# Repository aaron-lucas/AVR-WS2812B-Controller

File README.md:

LED Strip Controller
==========================

Project Description:
---------------------
This project uses an Atmel ATtiny85 microcontroller to light up a strip of WS2812B LEDs with a set of 12 pre-defined patterns without relying on external libraries.

It is easy to create custom patterns as each LED is independently controlled.

A PCB design is included which allows the microcontroller and LED strip to be powered over a micro USB (type B) connection, with a toggle switch to turn the LED strip on or off and a Cherry-MX style button to cycle between the display modes.

Colors and Patterns:
---------------------

There are 12 pre-defined patterns programmed by default including 9 solid colors, an auto-cycle mode, disco mode and rainbow fade mode. The 9 pre-defined colors and their RGB hex values are as follows:

* Red               [0xC00000]
* Green             [0x206000]
* Purple            [0x6E00FF]
* Orange            [0xFF2000]
* Blue              [0x001080]
* White             [0x867565]
* Pink              [0xFF009A]
* Yellow            [0xEA5200]
* Light blue/cyan   [0x00777A]

Theoretically, some of these colors are inaccurate (e.g. the RGB combination for yellow is actually orange), however due to the different intensities of the individual red, green and blue LEDs, these color definitions show the correct color when displayed on the WS2812B LED strip.

**Auto-cycle mode** cycles through the above solid colors in order from top to bottom, showing each color for a pre-defined time interval (currently set to 7s).

**Disco mode** gives each LED a random color from the above list (excluding white), which changes every 25ms.

**Rainbow fade mode** slowly transitions all LEDS in a cycle from red to green to blue to red (and so on).

The modes are cycled in the order they are listed in above, starting from solid red. When the toggle button is pressed in rainbow fade mode, the pattern will cycle back around to solid red.

Limitations:
-------------
Since the LED colors are programmed without an external library, the communication with the LED strip is done using a custom function written in assembly which determines the correct signal timing by counting clock cycles. The number of clock cycles required to send the correct data has been tuned for a 16MHz clock frequency and therefore in order to display the correct colors, 16MHz is the only frequency which may be used.

Each LED is given its own memory location which defines the RGB color components and allows each LED to be set independently. However, since the ATtiny85 contains only 512 bytes of SRAM then the number of LEDs which can be controlled by this MCU is limited. The controller program utilises 20 bytes of data memory leaving 492 bytes for RGB data and stack memory. The minimum stack size required is approximately 22 bytes and the RGB data consists of 3 bytes per LED meaning a maximum of 156 LEDs can be controlled with the ATtiny85 - more would require a microcontroller with more SRAM. This is enough to control a 2m strip with 60LEDs/m (120 LEDs total) or a 5m strip with 30LEDs/m (150 LEDs total) which are both commonly found configurations.

Depending on the number of LEDs used and the pattern being displayed, the total current draw can exceed 2A which may exceed the safe limits of cheaper USB cables. It is recommended to use a cable with a high current rating.

Equipment Used:
----------------
* [Jaycar's 2M Addressable LED Strip](https://www.jaycar.com.au/2m-rgb-led-strip-with-120-x-addressable-w2812b-rgb-leds-arduino-mcu-compatible-5v/p/XC4390) 
* [ATtiny85 DIP8](https://www.microchip.com/wwwproducts/en/ATtiny85)
* [Jaycar's ISP Programmer (USBasp)](https://www.jaycar.com.au/isp-programmer-for-arduino-and-avr/p/XC4627)

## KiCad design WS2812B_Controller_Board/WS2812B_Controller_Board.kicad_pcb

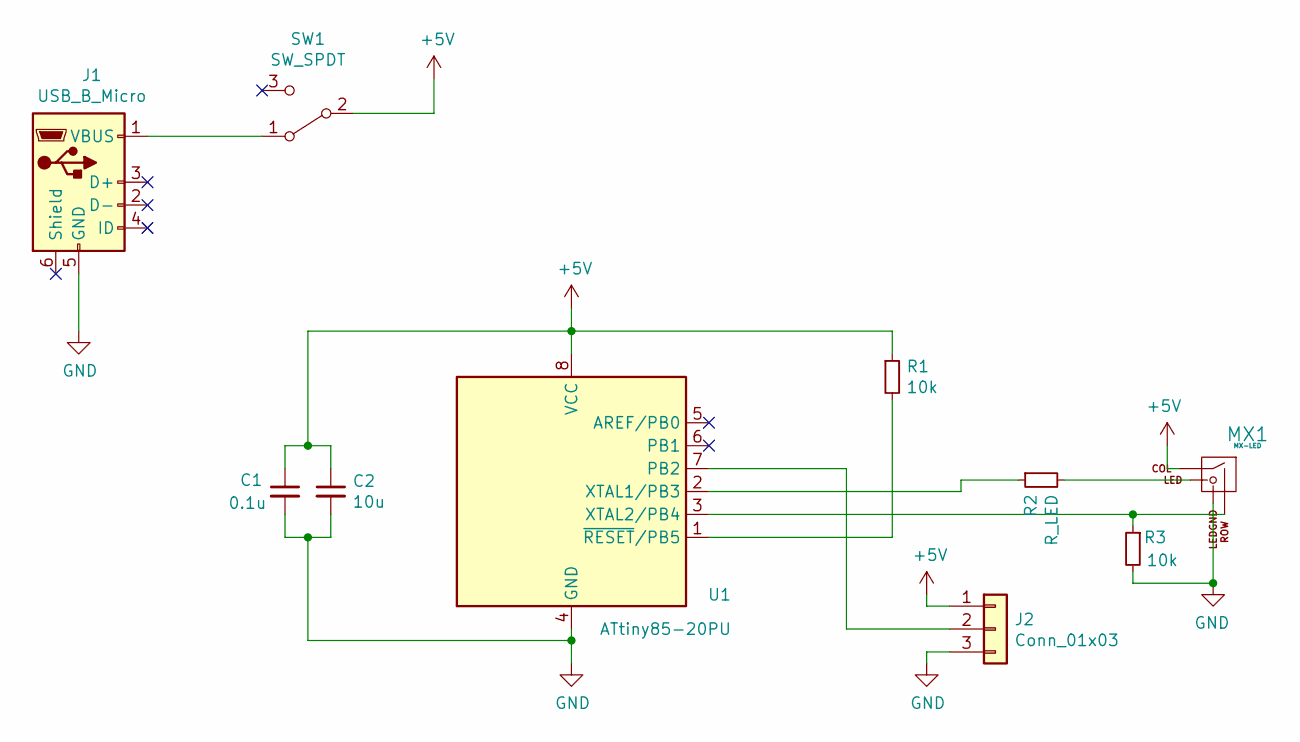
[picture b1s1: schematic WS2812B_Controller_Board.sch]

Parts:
C1: 0.1u; C_Disc_D4.3mm_W1.9mm_P5.00mm
C2: 10u; C_Radial_D5.0mm_H11.0mm_P2.00mm
J1: USB_B_Micro; USB_Micro-B_Amphenol_10103594-0001LF_Horizontal
J2: Conn_01x03; SolderWirePad_1x03_P3.175mm_Drill1mm
MX1: MX-LED; MX-1U
R1, R3: 10k; R_Axial_DIN0207_L6.3mm_D2.5mm_P10.16mm_Horizontal
R2: R_LED; R_Axial_DIN0207_L6.3mm_D2.5mm_P10.16mm_Horizontal
SW1: SW_SPDT; SPDT_Toggle_Switch_Jaycar_ST0546
U1: ATtiny85-20PU; DIP-8_W7.62mm

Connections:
+5V: C1.1, C2.1, J2.1, MX1.1 (COL), R1.1, SW1.2 (B), U1.8 (VCC)
GND: C1.2, C2.2, J1.5 (GND), J2.3, MX1.4 (LEDGND), R3.2, U1.4 (GND)
unnamed: J1.1 (VBUS), SW1.1 (A)
unnamed: J2.2, U1.7 (PB2)
unnamed: MX1.2 (ROW), R3.1, U1.3 (XTAL2/PB4)
unnamed: MX1.3 (LED), R2.2
unnamed: R1.2, U1.1 (~RESET~/PB5)
unnamed: R2.1, U1.2 (XTAL1/PB3)

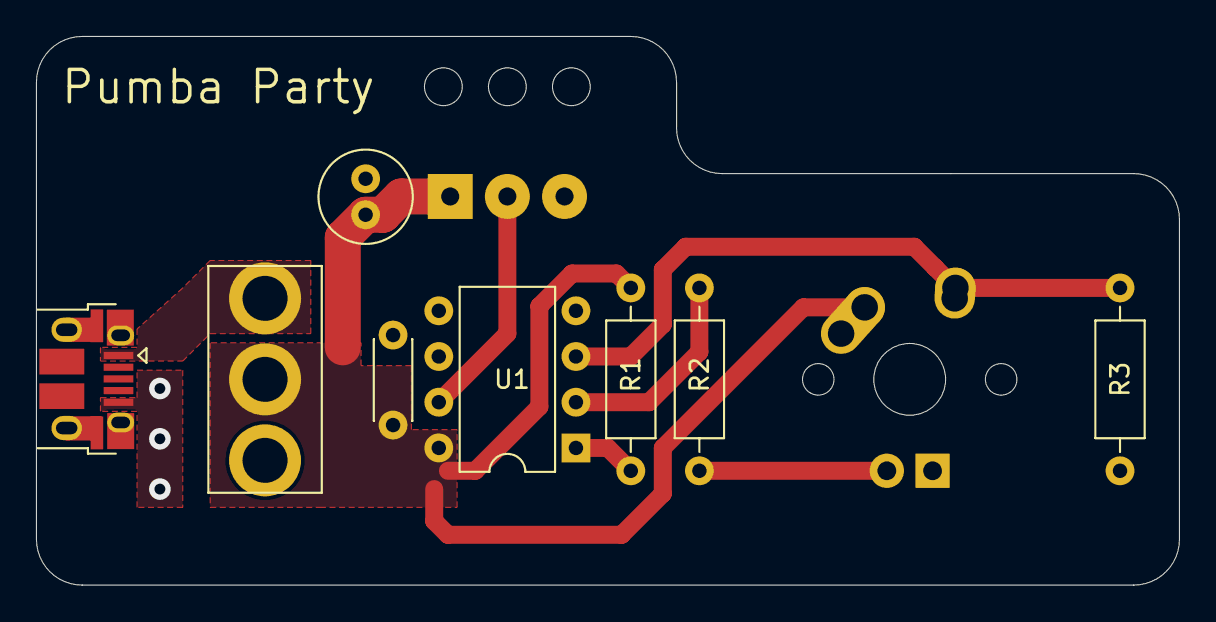
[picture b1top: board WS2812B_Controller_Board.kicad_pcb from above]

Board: 2 copper layers, 63.5 x 30.5 mm, 10 parts (0 on the bottom side), 8 nets.

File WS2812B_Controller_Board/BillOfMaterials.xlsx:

PCB Reference | Description | Package | Link
C1 | 0.1uF Capacitor | THT - Disc (Diameter: 4.3mm, Wdith: 1.9mm, Pitch: 5.0mm) | Generic
C2 | 10uF Capacitor | THT - Radial (Diameter: 5.0mm, Pitch: 2.0mm) | Generic
J1 | Micro-B USB connector, Amphenol 10103594-0001LF | SMD (5-pin) | https://au.mouser.com/ProductDetail/fci-amphenol/10103594-00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
J2 | N/A
MX1 | Cherry-MX style switch | THT - generic cherry switch | Generic
R1 | 10k resistor | THT - Axial (Length: 6.3mm, Diameter: 2.5mm, Pitch: 10.16mm) | Generic
R2 | Resistor (unspecified value) | THT - Axial (Length: 6.3mm, Diameter: 2.5mm, Pitch: 10.16mm) | Generic
R3 | 10k resistor | THT - Axial (Length: 6.3mm, Diameter: 2.5mm, Pitch: 10.16mm) | Generic
SW1 | SPDT toggle switch | THT - 3-pin Linear (Length: 12mm, Width: 7mm, Pitch: 4.5mm, Pin: 0.9mm x 2.1mm | https://www.jaycar.com.au/spdt-flattened-actuator-mini-toggl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
U1 | ATtiny85 Microcontroller | THT - DIP8 | https://au.mouser.com/ProductDetail/microchip/attiny85-20pu/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
U1 | 8-pin DIP Mill-Max IC socket | THT - DIP8 | https://au.mouser.com/ProductDetail/mill-max/110-44-308-41-0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

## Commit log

2020-12-10 Document Makefile and add details to README
2020-12-10 Modify formatting of README
2020-12-10 Remove unnecessary information from README
2020-12-16 Add PCB design, save SREG in .S function
2020-12-27 Finish circuit board design
2020-12-29 Allow up to 156 LEDs to be used.
    Perform SRAM optimisations, update README and add debugging targets to Makefile.
2021-05-21 Clean up project, add BOM/footprints
